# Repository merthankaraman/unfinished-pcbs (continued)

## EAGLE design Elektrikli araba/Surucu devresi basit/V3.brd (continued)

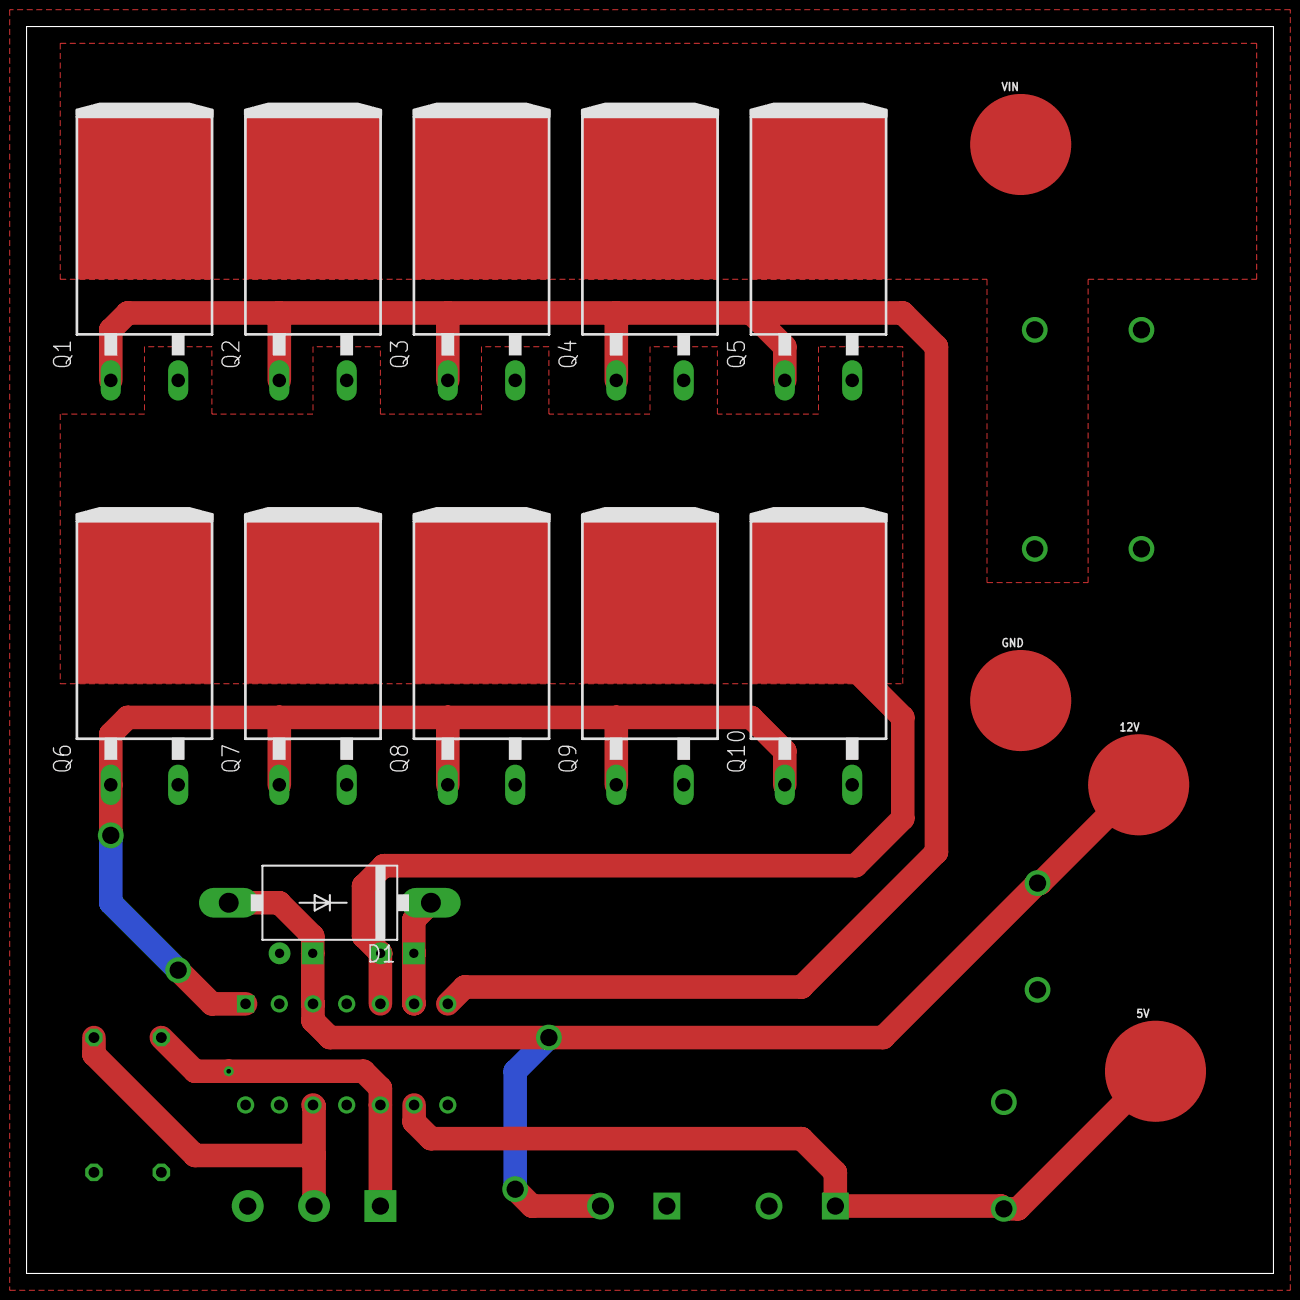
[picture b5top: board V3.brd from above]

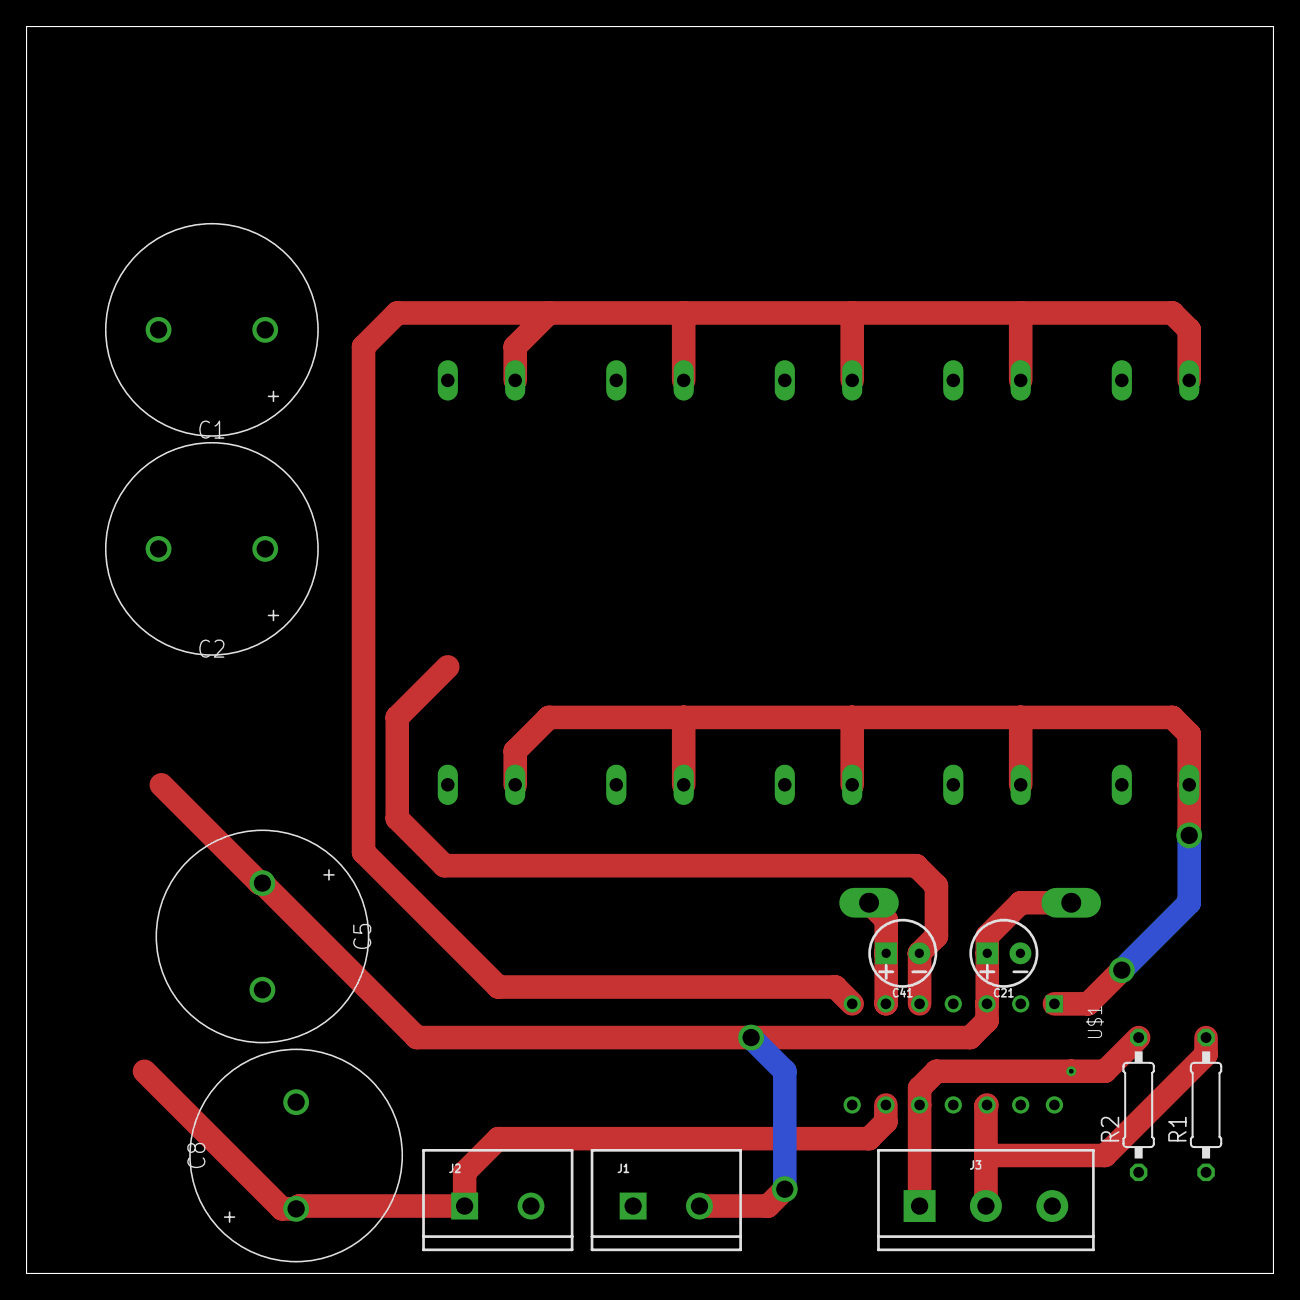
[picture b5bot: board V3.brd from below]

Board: 2 copper layers, 94.0 x 94.0 mm, 27 parts (12 on the bottom side), 10 nets.

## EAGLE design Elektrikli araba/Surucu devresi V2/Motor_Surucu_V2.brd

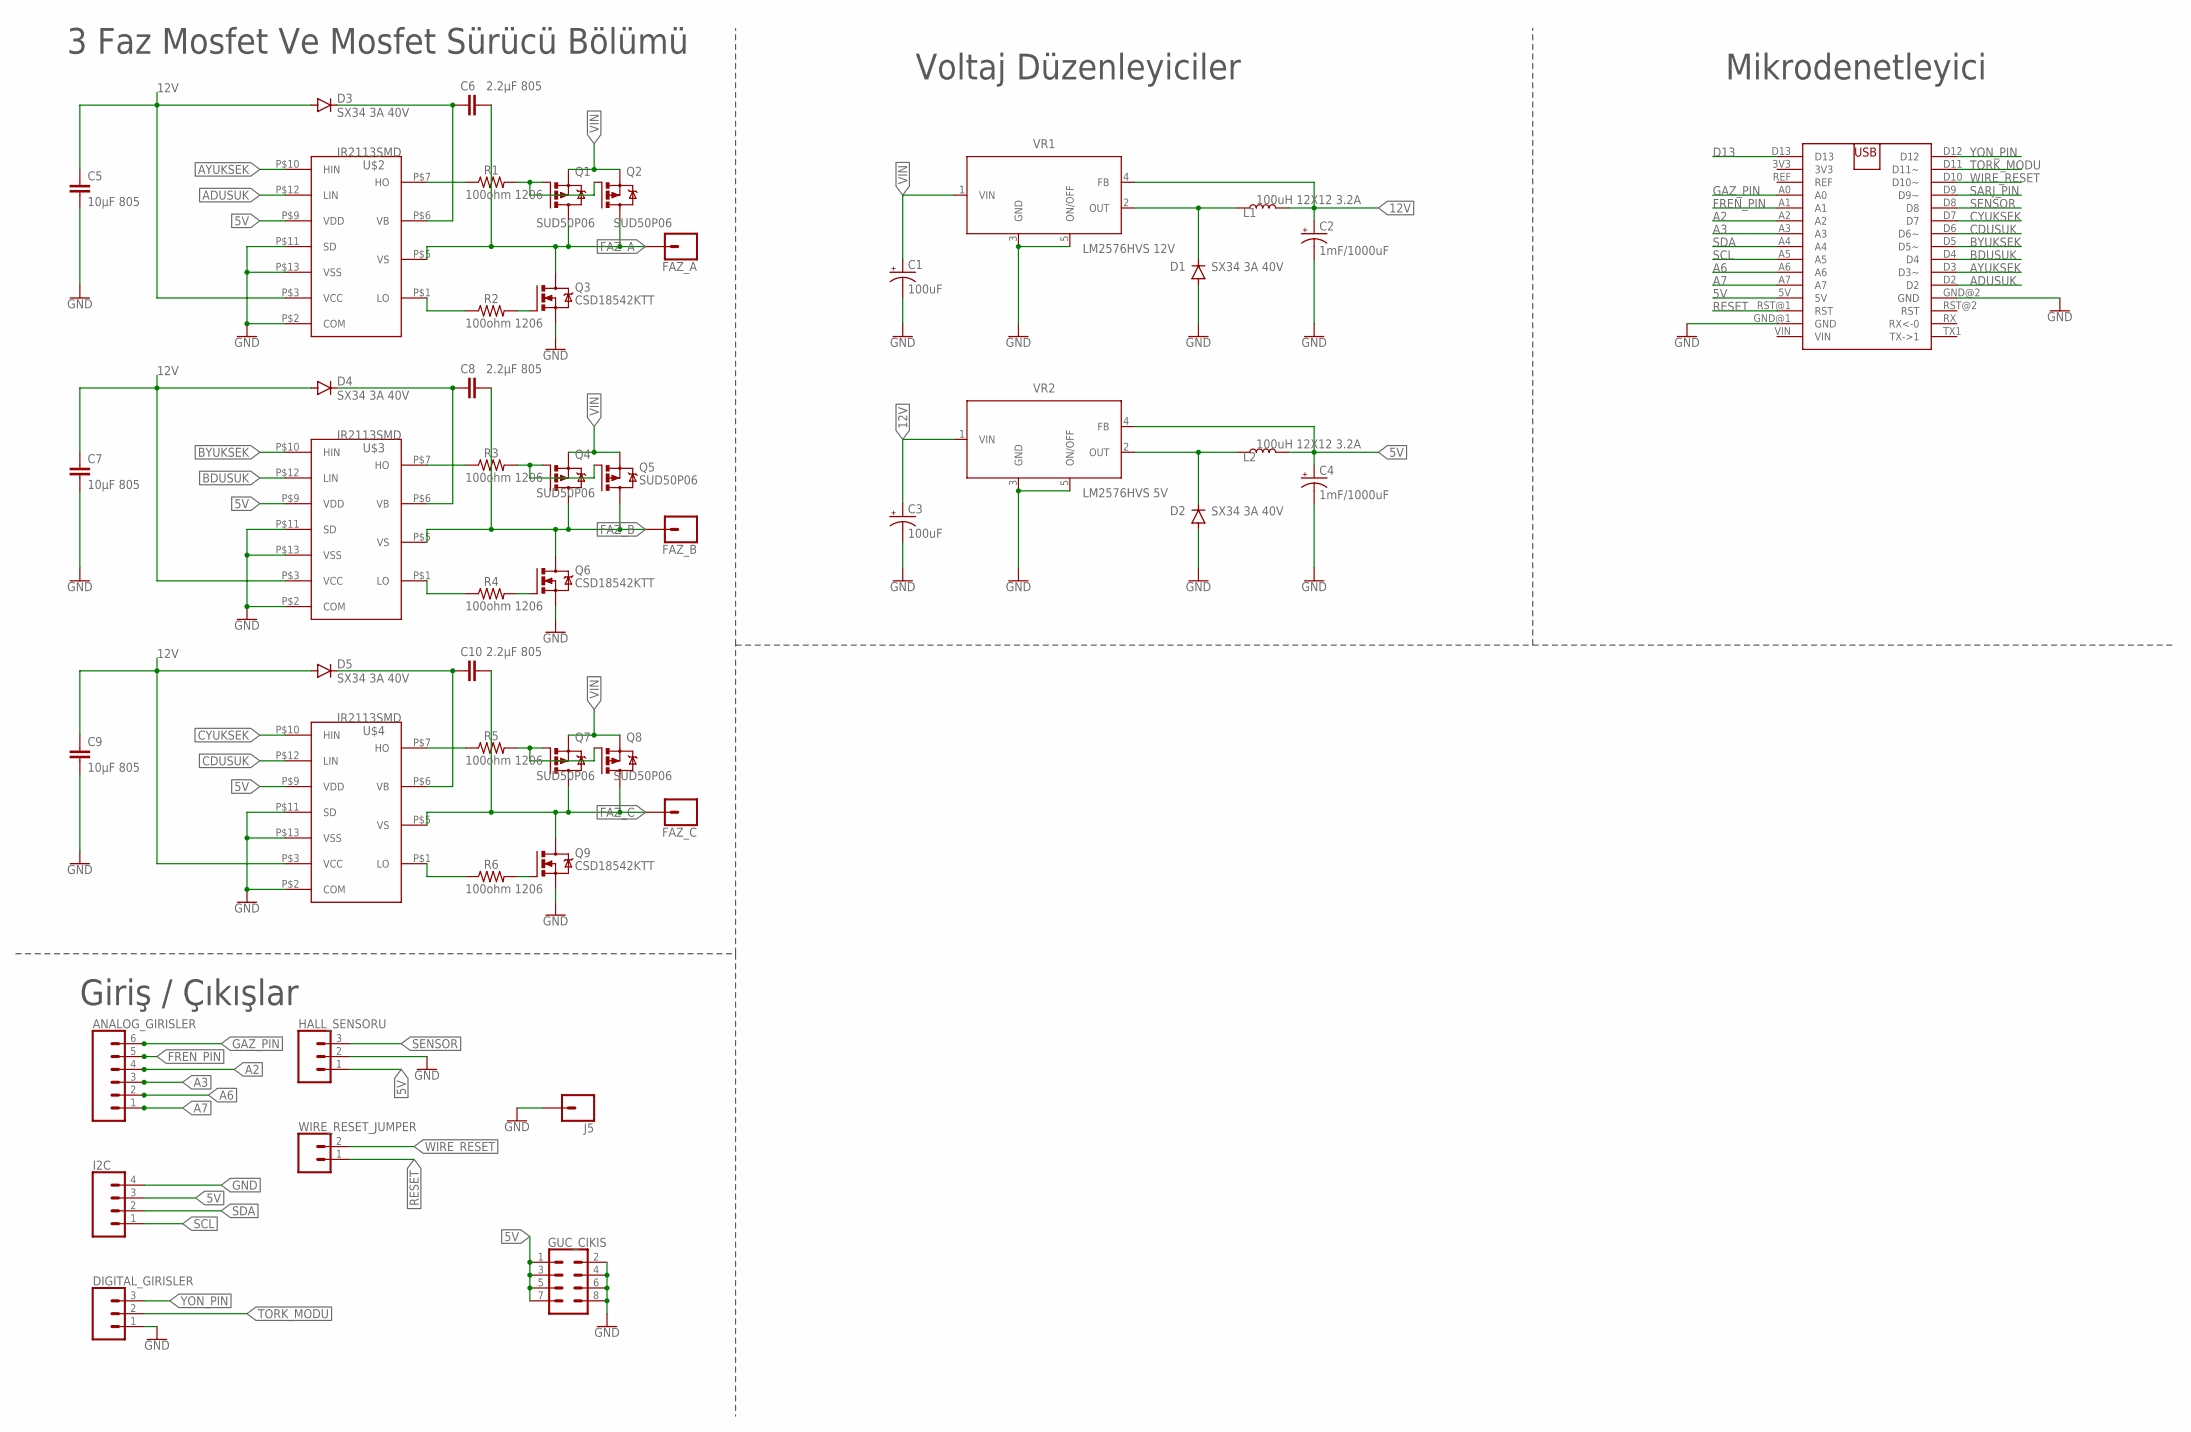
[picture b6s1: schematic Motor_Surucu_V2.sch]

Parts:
ANALOG_GIRISLER: CONN_06SILK_FEMALE_PTH; 1X06
C1, C3: 100uF; CPOL-RADIAL-2.5MM-6.5MM
C2, C4: 1mF/1000uF; PANASONIC_G
C5, C7, C9: 10µF 805; 0805
C6, C8, C10: 2.2µF 805; 0805
D1, D2, D3, D4, D5: SX34 3A 40V; DO214AC
DIGITAL_GIRISLER: CONN_03; 1X03
FAZ_A: CONN_01SNAP-MALE; SNAP-MALE
FAZ_B: CONN_01SNAP-MALE; SNAP-MALE
FAZ_C: CONN_01SNAP-MALE; SNAP-MALE
GUC_CIKIS: CONN_04X2; 2X4
HALL_SENSORU: CONN_03; 1X03
I2C: CONN_04; 1X04
J5: CONN_01SNAP-MALE; SNAP-MALE
L1, L2: 100uH 12X12 3.2A; INDUCTOR_SDR1307
Q1, Q2, Q4, Q5, Q7, Q8: SUD50P06; TO-252
Q3, Q6, Q9: CSD18542KTT; TO263-3
R1, R2, R3, R4, R5, R6: 100ohm 1206; 1206
U$1: ARDUINO_NANO
U$2, U$3, U$4: IR2113SMD; SOIC-14
VR1: LM2576HVS 12V; TO170P1435X465-6N
VR2: LM2576HVS 5V; TO170P1435X465-6N
WIRE_RESET_JUMPER: CONN_02; 1X02

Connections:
5V: C4.+, GUC_CIKIS.1, GUC_CIKIS.3, GUC_CIKIS.5, GUC_CIKIS.7, HALL_SENSORU.1, I2C.3, L2.P$2 (2), U$1.5V, U$2.P$9 (VDD), U$3.P$9 (VDD), U$4.P$9 (VDD), VR2.4 (FB)
12V: C2.+, C3.1 (+), C5.1, C7.1, C9.1, D3.A, D4.A, D5.A, L1.P$2 (2), U$2.P$3 (VCC), U$3.P$3 (VCC), U$4.P$3 (VCC), VR1.4 (FB), VR2.1 (VIN)
A2: ANALOG_GIRISLER.4, U$1.A2
A3: ANALOG_GIRISLER.3, U$1.A3
A6: ANALOG_GIRISLER.2, U$1.A6
A7: ANALOG_GIRISLER.1, U$1.A7
ADUSUK: U$1.D2, U$2.P$12 (LIN)
AYUKSEK: U$1.D3 (D3~), U$2.P$10 (HIN)
BDUSUK: U$1.D4, U$3.P$12 (LIN)
BYUKSEK: U$1.D5 (D5~), U$3.P$10 (HIN)
CDUSUK: U$1.D6 (D6~), U$4.P$12 (LIN)
CYUKSEK: U$1.D7, U$4.P$10 (HIN)
D13: U$1.D13
FAZ_A: C6.2, FAZ_A.2, Q1.TAB (D), Q2.TAB (D), Q3.TAB (D), U$2.P$5 (VS)
FAZ_B: C8.2, FAZ_B.2, Q4.TAB (D), Q5.TAB (D), Q6.TAB (D), U$3.P$5 (VS)
FAZ_C: C10.2, FAZ_C.2, Q7.TAB (D), Q8.TAB (D), Q9.TAB (D), U$4.P$5 (VS)
FREN_PIN: ANALOG_GIRISLER.5, U$1.A1
GAZ_PIN: ANALOG_GIRISLER.6, U$1.A0
GND: C1.2 (-), C2.-, C3.2 (-), C4.-, C5.2, C7.2, C9.2, D1.A, D2.A, DIGITAL_GIRISLER.1, GUC_CIKIS.2, GUC_CIKIS.4, GUC_CIKIS.6, GUC_CIKIS.8, HALL_SENSORU.2, I2C.4, J5.2, Q3.3 (S), Q6.3 (S), Q9.3 (S), U$1.GND@1 (GND), U$1.GND@2 (GND), U$2.P$2 (COM), U$2.P$11 (SD), U$2.P$13 (VSS), U$3.P$2 (COM), U$3.P$11 (SD), U$3.P$13 (VSS), U$4.P$2 (COM), U$4.P$11 (SD), U$4.P$13 (VSS), VR1.3 (GND), VR1.5 (ON/OFF), VR2.3 (GND), VR2.5 (ON/OFF)
unnamed: D2.C, L2.P$1 (1), VR2.2 (OUT)
unnamed: C6.1, D3.C, U$2.P$6 (VB)
unnamed: Q1.1 (G), Q2.1 (G), R1.2
unnamed: R1.1, U$2.P$7 (HO)
unnamed: Q3.1 (G), R2.2
unnamed: R2.1, U$2.P$1 (LO)
unnamed: C8.1, D4.C, U$3.P$6 (VB)
unnamed: Q4.1 (G), Q5.1 (G), R3.2
unnamed: R3.1, U$3.P$7 (HO)
unnamed: Q6.1 (G), R4.2
unnamed: R4.1, U$3.P$1 (LO)
unnamed: C10.1, D5.C, U$4.P$6 (VB)
unnamed: Q7.1 (G), Q8.1 (G), R5.2
unnamed: R5.1, U$4.P$7 (HO)
unnamed: Q9.1 (G), R6.2
unnamed: R6.1, U$4.P$1 (LO)
unnamed: D1.C, L1.P$1 (1), VR1.2 (OUT)
RESET: U$1.RST@1 (RST), WIRE_RESET_JUMPER.1
SARJ_PIN: U$1.D9 (D9~)
SCL: I2C.1, U$1.A5
SDA: I2C.2, U$1.A4
SENSOR: HALL_SENSORU.3, U$1.D8
TORK_MODU: DIGITAL_GIRISLER.2, U$1.D11 (D11~)
VIN: C1.1 (+), Q1.3 (S), Q2.3 (S), Q4.3 (S), Q5.3 (S), Q7.3 (S), Q8.3 (S), VR1.1 (VIN)
WIRE_RESET: U$1.D10 (D10~), WIRE_RESET_JUMPER.2
YON_PIN: DIGITAL_GIRISLER.3, U$1.D12

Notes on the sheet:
3 Faz Mosfet Ve Mosfet Sürücü Bölümü
Voltaj Düzenleyiciler
Mikrodenetleyici
Giriş / Çıkışlar

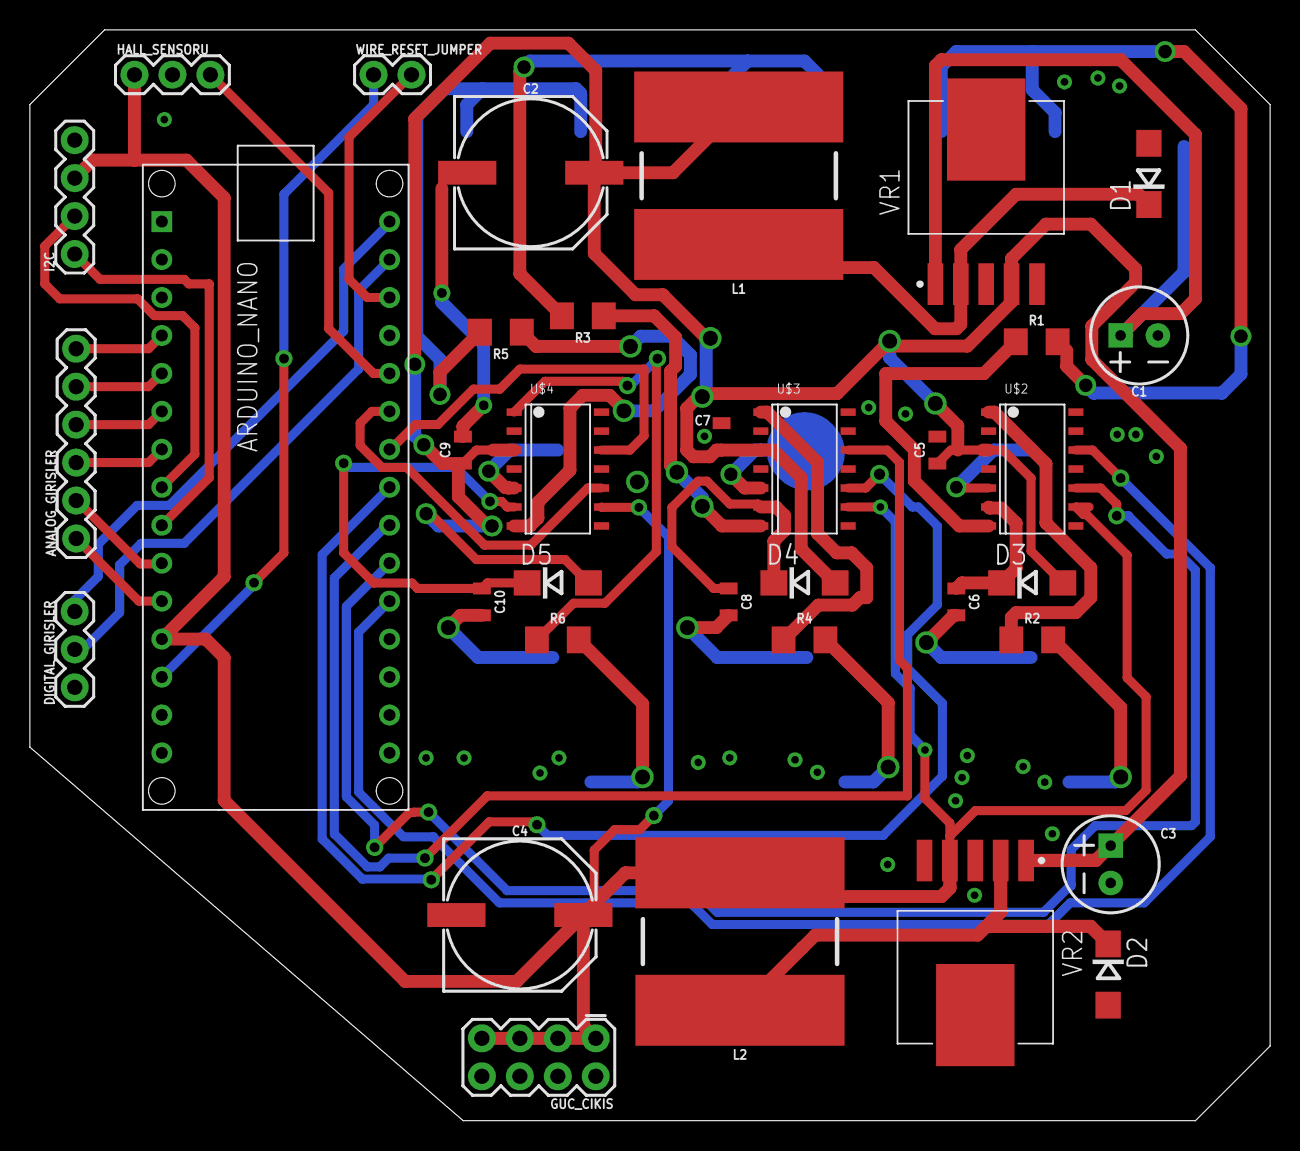
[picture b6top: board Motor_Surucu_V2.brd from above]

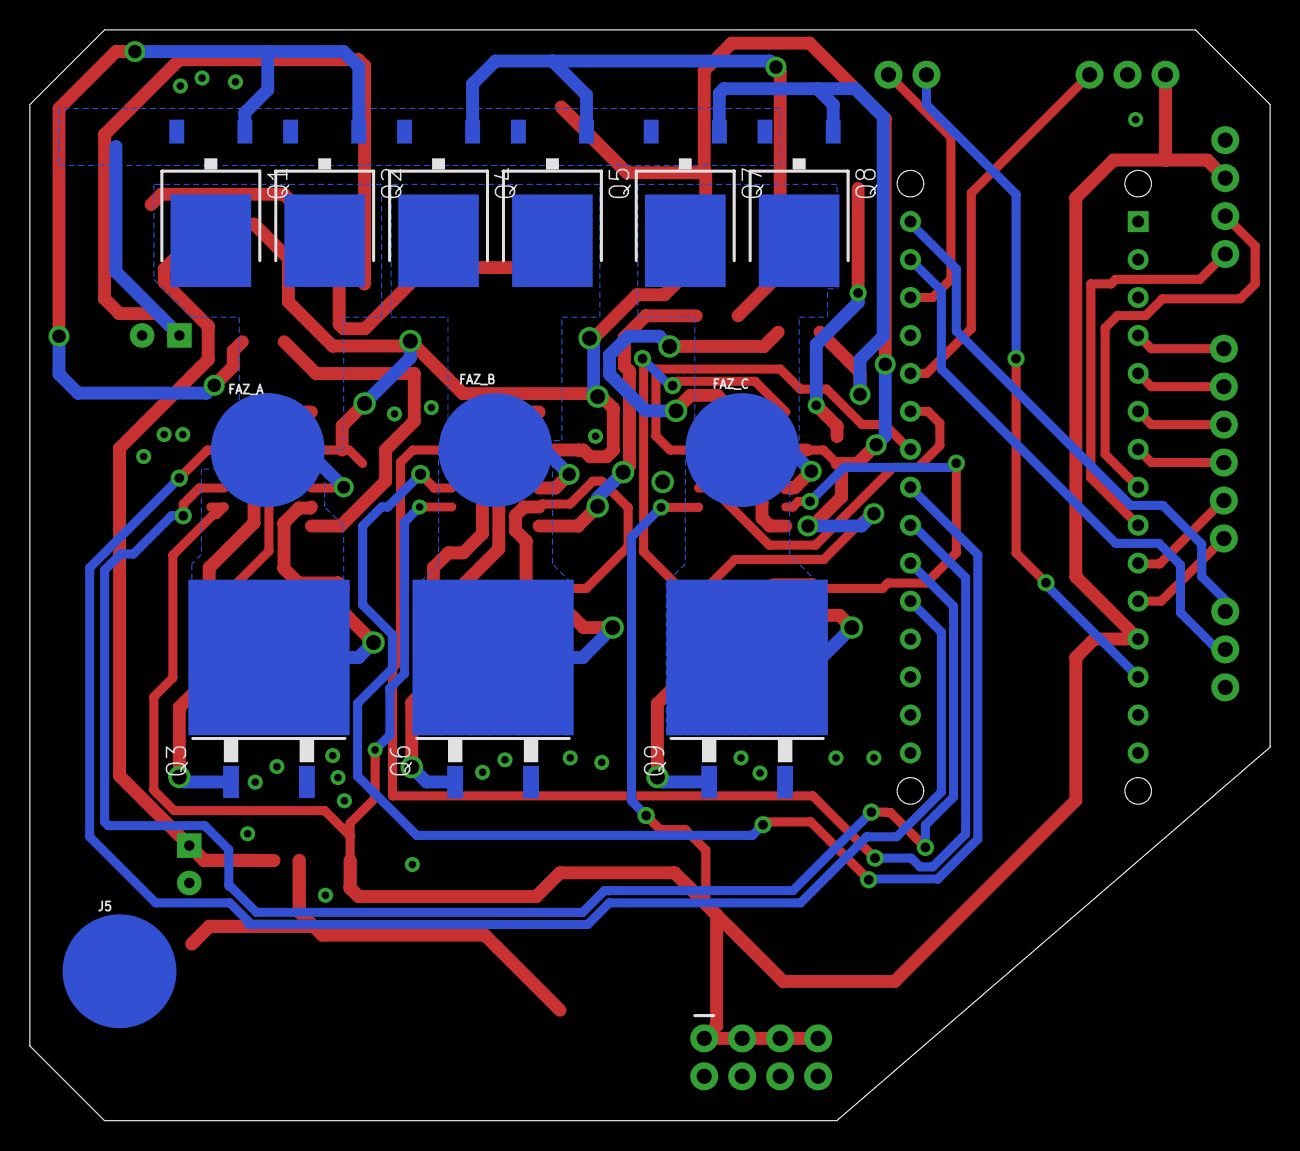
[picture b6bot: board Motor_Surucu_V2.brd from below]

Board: 2 copper layers, 83.0 x 73.0 mm, 48 parts (13 on the bottom side), 43 nets.

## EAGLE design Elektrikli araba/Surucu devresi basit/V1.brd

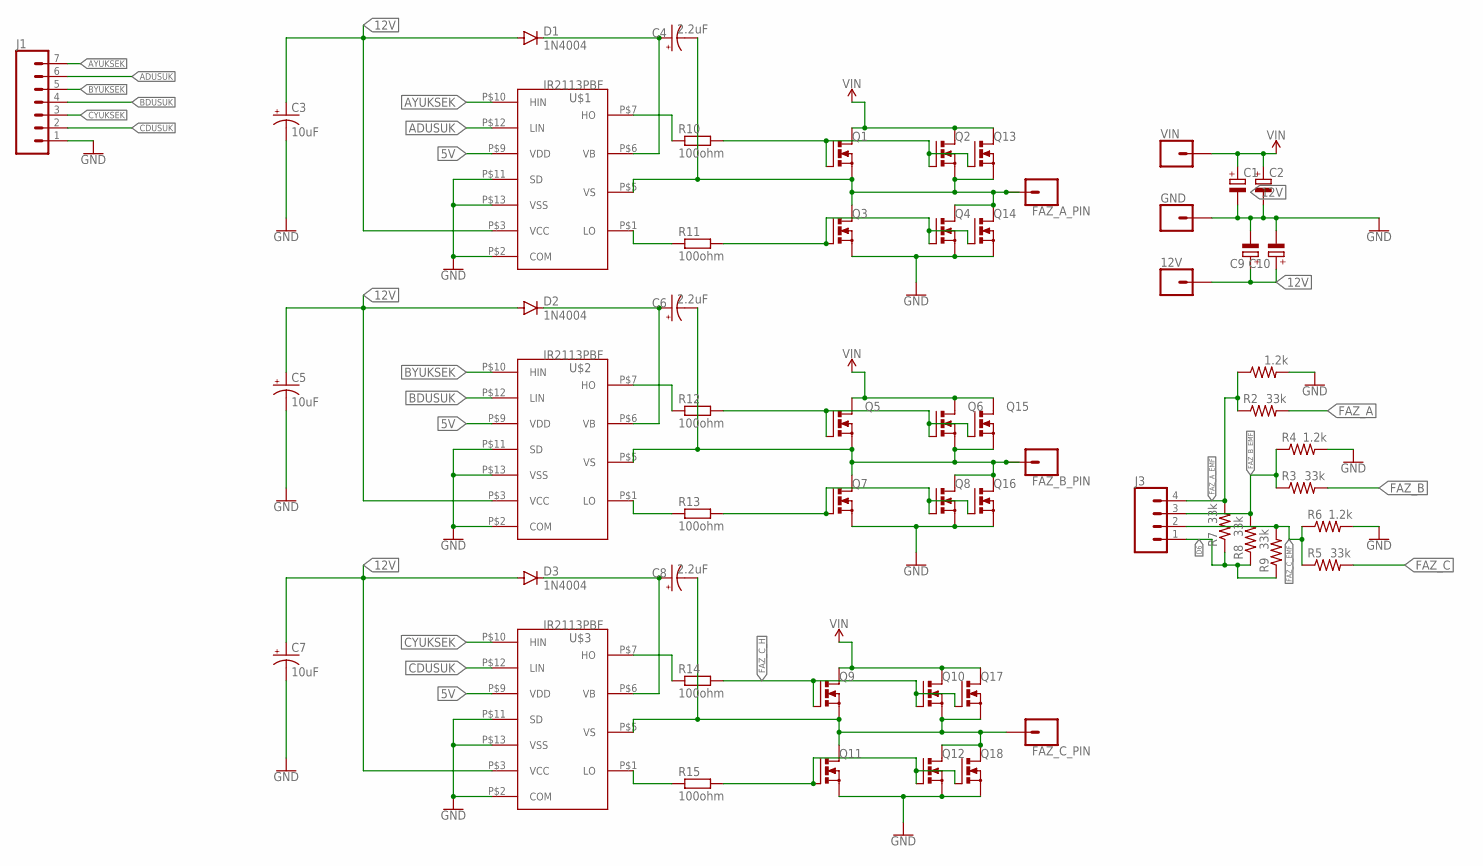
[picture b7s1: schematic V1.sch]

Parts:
12V: CONN_01SNAP-MALE; SNAP-MALE
C1, C2, C9, C10: C-POL_RADIAL-25MM-DIA; CAPPRD550W110D1250H2500B
C3, C5, C7: 10uF; CPOL-RADIAL-2.5MM-5MM
C4, C6, C8: 2.2uF; CPOL-RADIAL-2.5MM-5MM
D1, D2, D3: 1N4004; DO41-10
FAZ_A_PIN: CONN_01SNAP-MALE; SNAP-MALE
FAZ_B_PIN: CONN_01SNAP-MALE; SNAP-MALE
FAZ_C_PIN: CONN_01SNAP-MALE; SNAP-MALE
GND: CONN_01SNAP-MALE; SNAP-MALE
J1: CONN_07; 1X07
J3: CONN_04; 1X04
Q1, Q2, Q3, Q4, Q5, Q6, Q7, Q8, Q9, Q10, Q11, Q12, Q13, Q14, Q15, Q16, Q17, Q18: PMOSFET_NTO220BV; TO220BV
R1, R4, R6: 1.2k; AXIAL-0.3
R2, R3, R5, R7, R8, R9: 33k; AXIAL-0.3
R10, R11, R12, R13, R14, R15: 100ohm; 0207/10
U$1, U$2, U$3: IR2113PBF; PDIP-14
VIN: CONN_01SNAP-MALE; SNAP-MALE

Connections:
5V: U$1.P$9 (VDD), U$2.P$9 (VDD), U$3.P$9 (VDD)
12V: 12V.2, C3.1 (+), C5.1 (+), C7.1 (+), C9.1 (+), C10.1 (+), D1.A, D2.A, D3.A, U$1.P$3 (VCC), U$2.P$3 (VCC), U$3.P$3 (VCC)
ADUSUK: J1.6, U$1.P$12 (LIN)
AYUKSEK: J1.7, U$1.P$10 (HIN)
BDUSUK: J1.4, U$2.P$12 (LIN)
BYUKSEK: J1.5, U$2.P$10 (HIN)
CDUSUK: J1.2, U$3.P$12 (LIN)
CYUKSEK: J1.3, U$3.P$10 (HIN)
D6: J3.1, R7.P$1 (1), R8.P$1 (1), R9.P$1 (1)
FAZ_A: C4.2 (-), FAZ_A_PIN.2, Q1.S, Q2.S, Q3.D, Q4.D, Q13.S, Q14.D, R2.P$2 (2), U$1.P$5 (VS)
FAZ_A_EMF: J3.4, R1.P$1 (1), R2.P$1 (1), R7.P$2 (2)
FAZ_A_H: Q1.G, Q2.G, Q13.G, R10.2
FAZ_A_L: Q3.G, Q4.G, Q14.G, R11.2
FAZ_B: C6.2 (-), FAZ_B_PIN.2, Q5.S, Q6.S, Q7.D, Q8.D, Q15.S, Q16.D, R3.P$2 (2), U$2.P$5 (VS)
FAZ_B_EMF: J3.3, R3.P$1 (1), R4.P$1 (1), R8.P$2 (2)
FAZ_B_H: Q5.G, Q6.G, Q15.G, R12.2
FAZ_B_L: Q7.G, Q8.G, Q16.G, R13.2
FAZ_C: C8.2 (-), FAZ_C_PIN.2, Q9.S, Q10.S, Q11.D, Q12.D, Q17.S, Q18.D, R5.P$2 (2), U$3.P$5 (VS)
FAZ_C_EMF: J3.2, R5.P$1 (1), R6.P$1 (1), R9.P$2 (2)
FAZ_C_H: Q9.G, Q10.G, Q17.G, R14.2
FAZ_C_L: Q11.G, Q12.G, Q18.G, R15.2
GND: C1.2 (-), C2.2 (-), C3.2 (-), C5.2 (-), C7.2 (-), C9.2 (-), C10.2 (-), GND.2, J1.1, Q3.S, Q4.S, Q7.S, Q8.S, Q11.S, Q12.S, Q14.S, Q16.S, Q18.S, R1.P$2 (2), R4.P$2 (2), R6.P$2 (2), U$1.P$2 (COM), U$1.P$11 (SD), U$1.P$13 (VSS), U$2.P$2 (COM), U$2.P$11 (SD), U$2.P$13 (VSS), U$3.P$2 (COM), U$3.P$11 (SD), U$3.P$13 (VSS)
unnamed: C6.1 (+), D2.C, U$2.P$6 (VB)
unnamed: R13.1, U$2.P$1 (LO)
unnamed: R12.1, U$2.P$7 (HO)
unnamed: C4.1 (+), D1.C, U$1.P$6 (VB)
unnamed: C8.1 (+), D3.C, U$3.P$6 (VB)
unnamed: R10.1, U$1.P$7 (HO)
unnamed: R15.1, U$3.P$1 (LO)
unnamed: R11.1, U$1.P$1 (LO)
unnamed: R14.1, U$3.P$7 (HO)
VIN: C1.1 (+), C2.1 (+), Q1.D, Q2.D, Q5.D, Q6.D, Q9.D, Q10.D, Q13.D, Q15.D, Q17.D, VIN.2

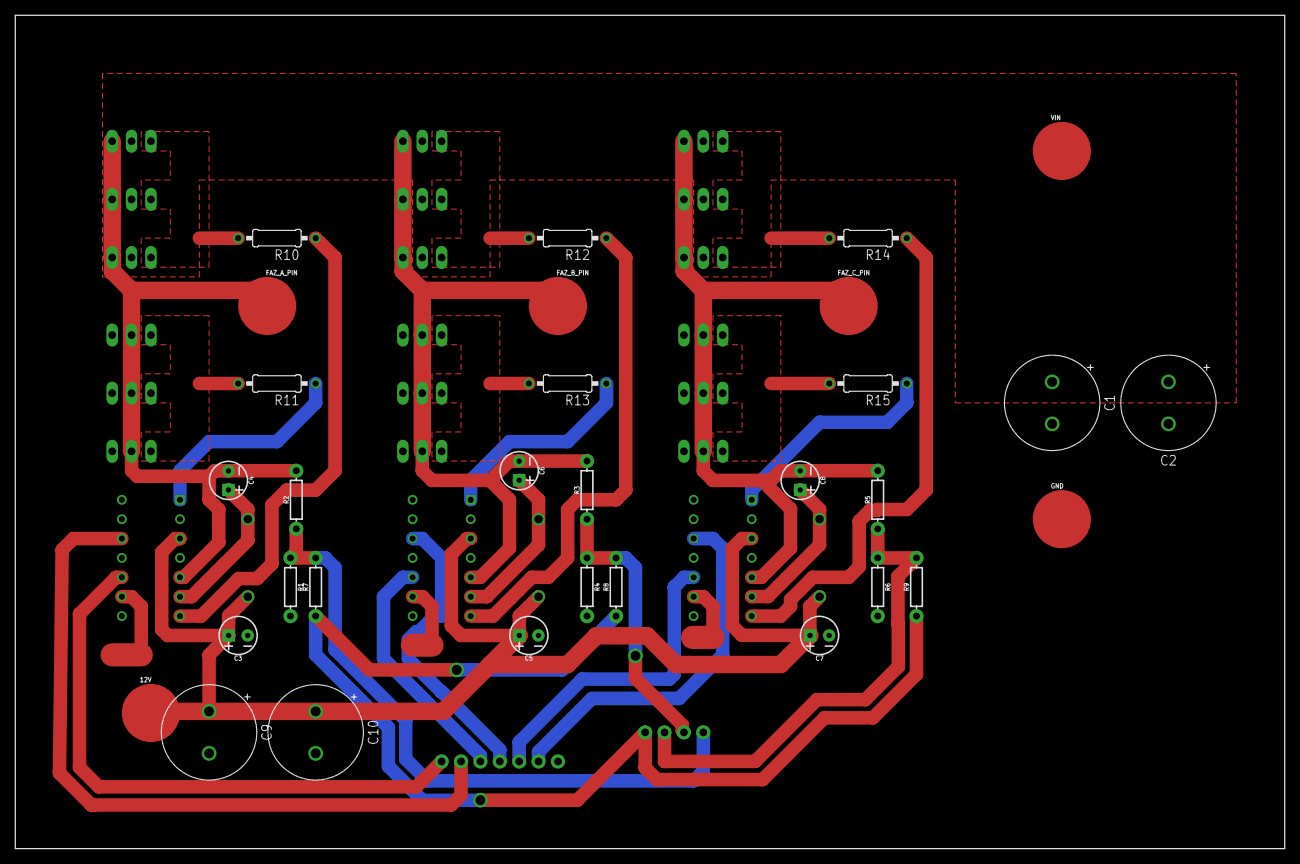
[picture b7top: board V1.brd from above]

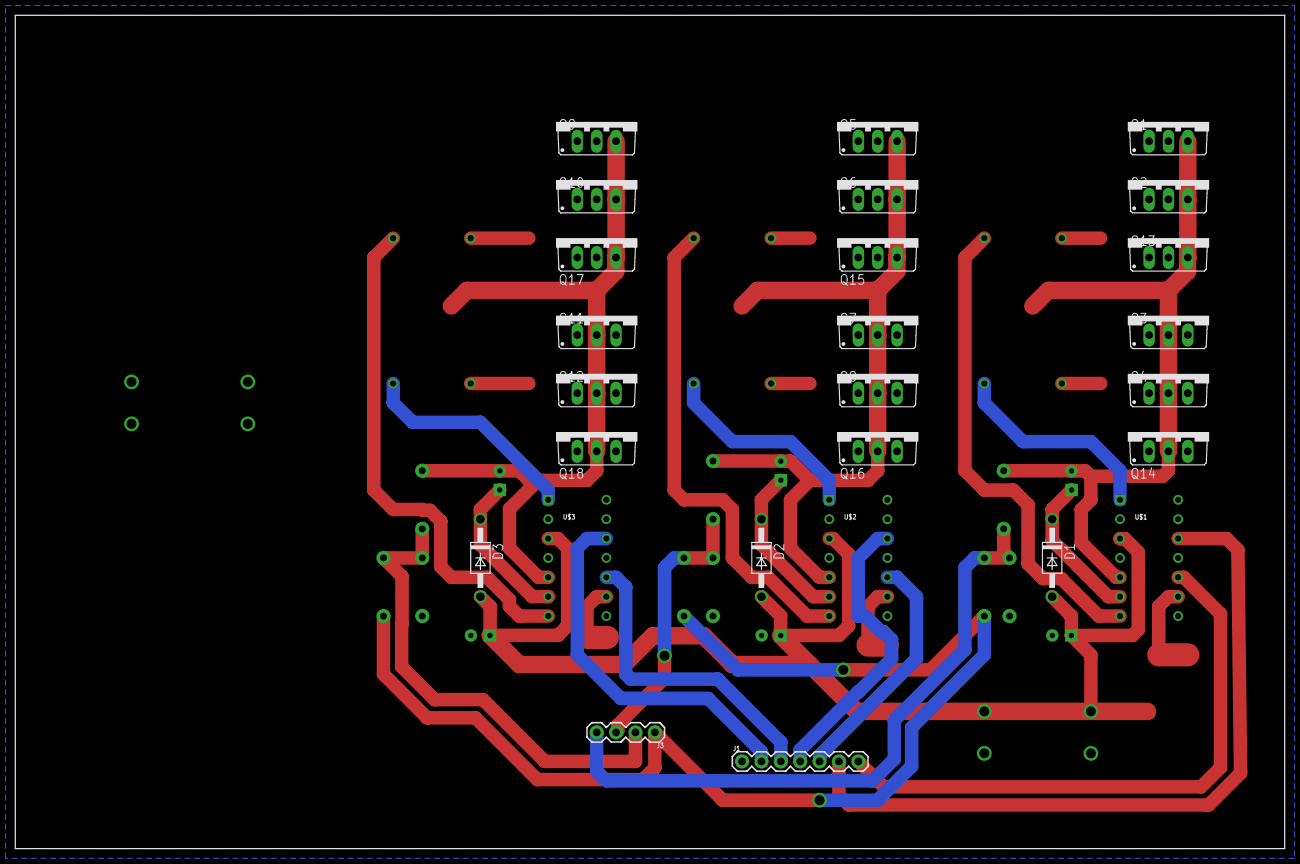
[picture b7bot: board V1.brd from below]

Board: 2 copper layers, 166.4 x 109.2 mm, 57 parts (26 on the bottom side), 32 nets.

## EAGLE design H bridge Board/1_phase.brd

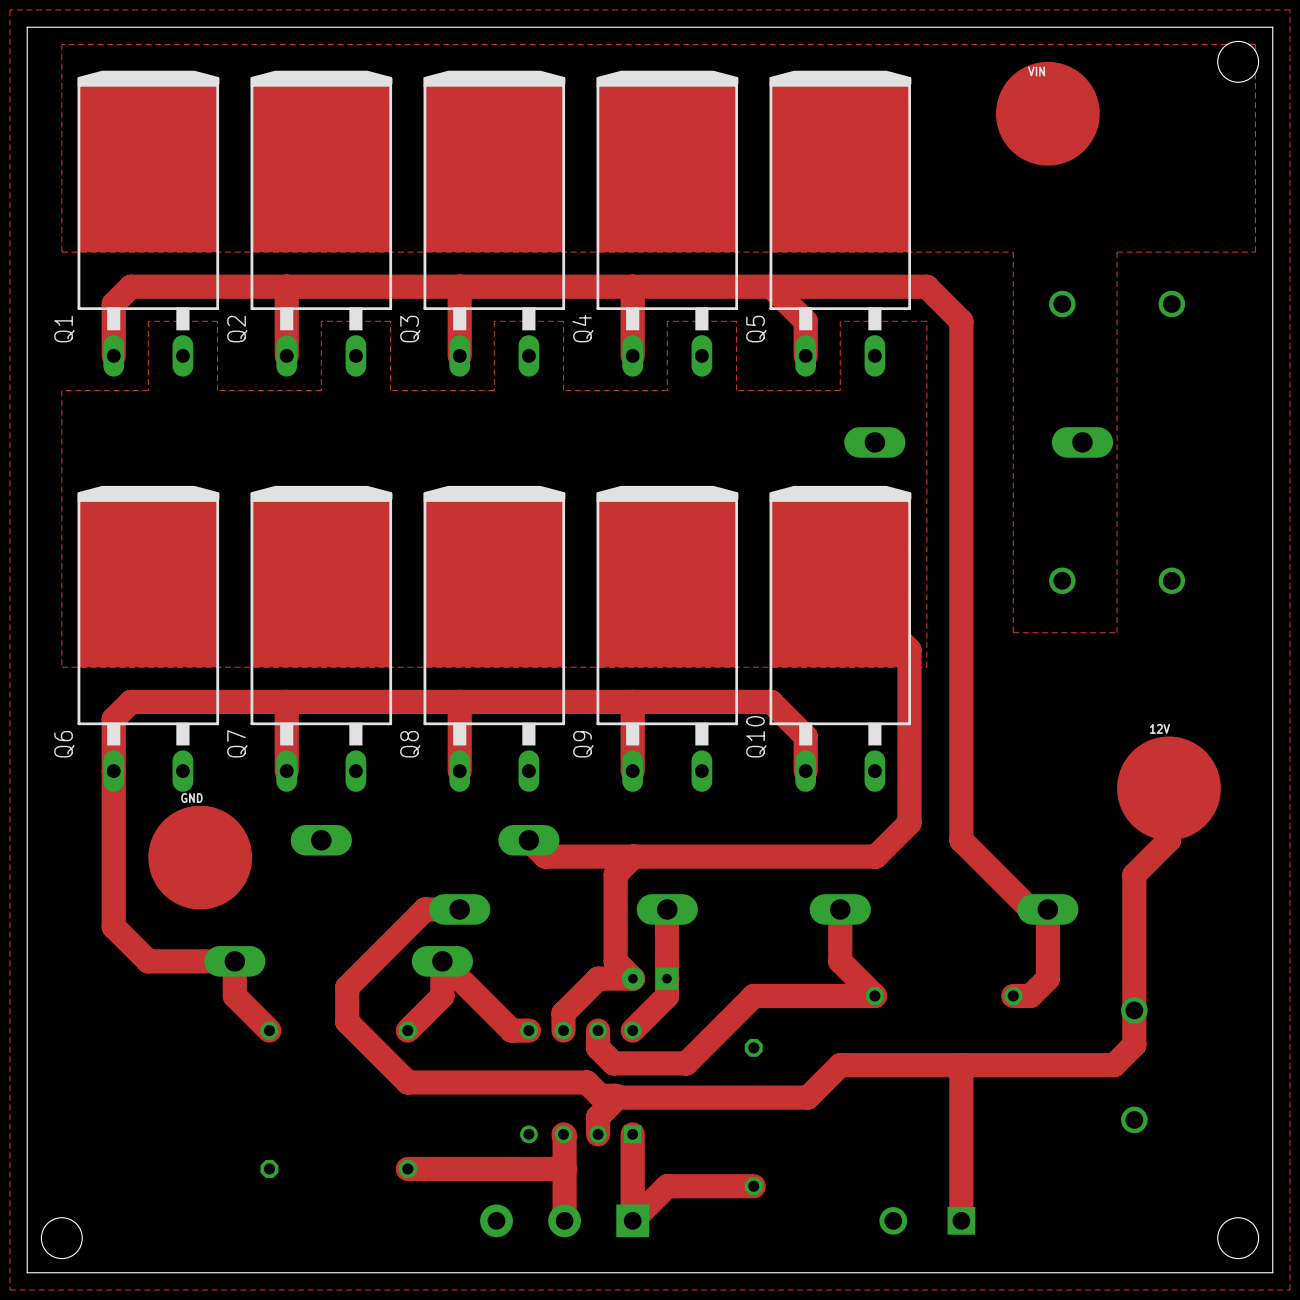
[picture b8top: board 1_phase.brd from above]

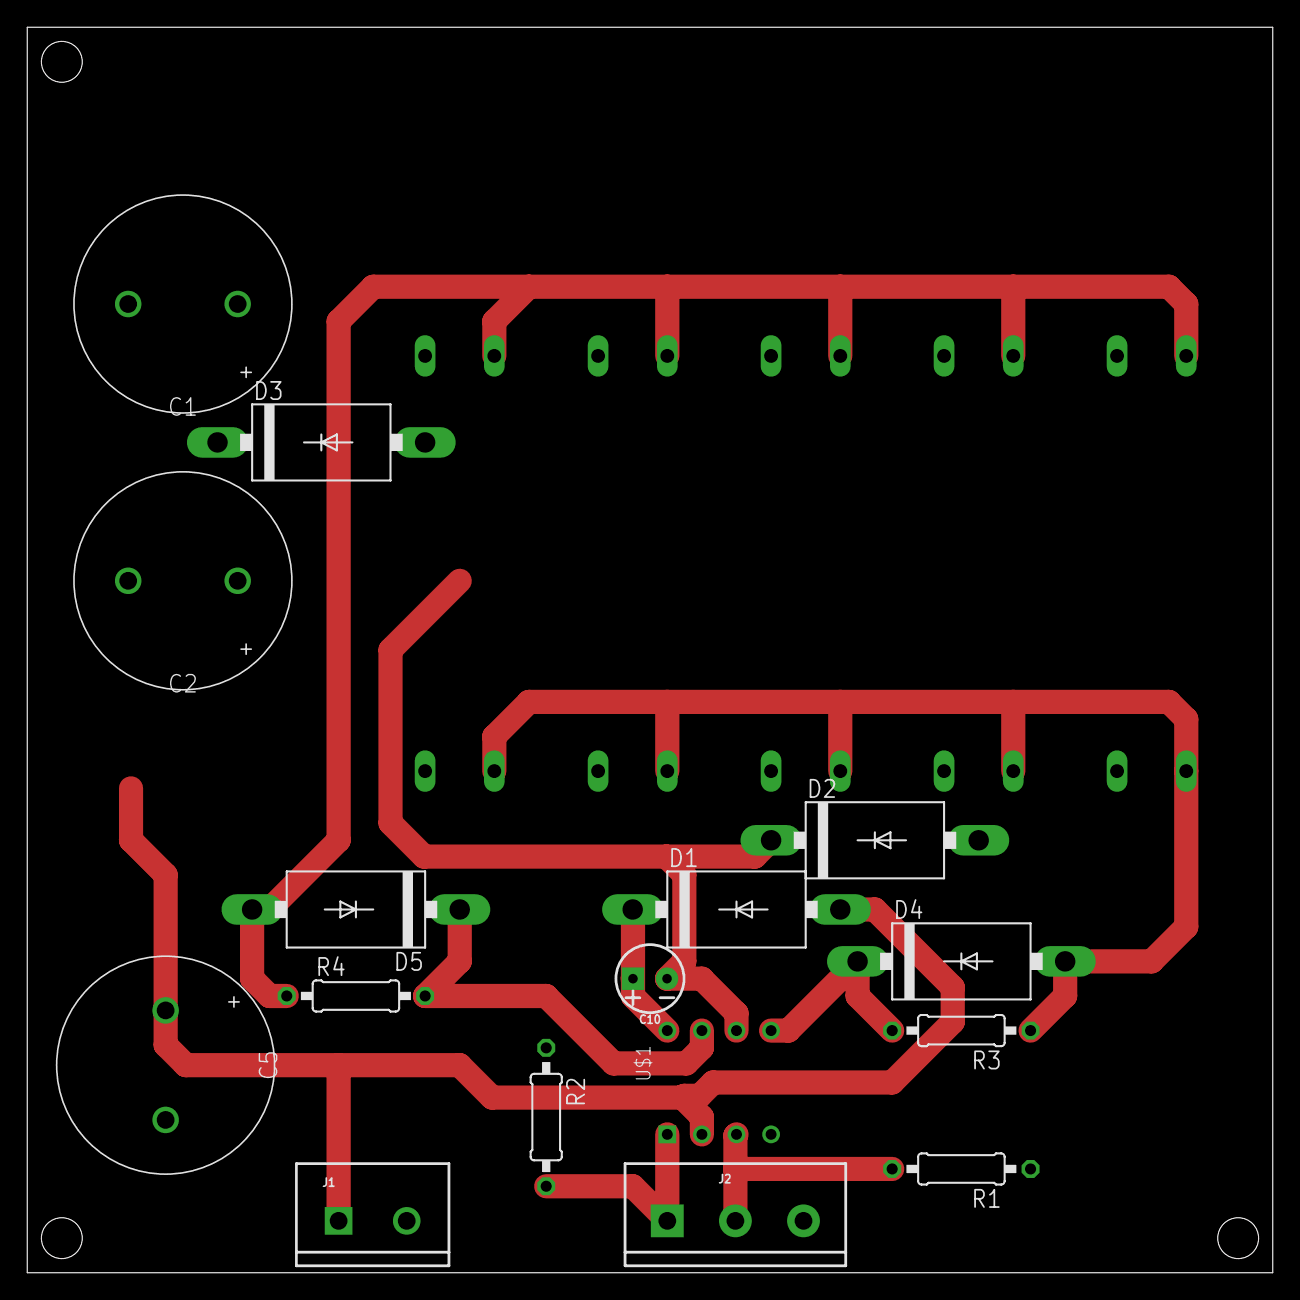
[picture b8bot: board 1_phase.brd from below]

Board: 2 copper layers, 91.4 x 91.4 mm, 29 parts (16 on the bottom side), 11 nets.

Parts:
12V: SNAP-MALE
C1, C2, C5: 16MM-DIA-CAPASITOR
C10: 2.2uF; CPOL-RADIAL-2.5MM-5MM
D1, D2, D3, D4, D5: 1N5400; DO201-15
GND: SNAP-MALE
J1: SCREWTERMINAL-5MM-2
J2: SCREWTERMINAL-5MM-3
Q1, Q2, Q3, Q4, Q5, Q6, Q7, Q8, Q9, Q10: IRF640N; TO-220-PAD
R1, R2: 10k; 0207/10
R3, R4: 27; 0207/10
U$1: IR2104PBF; DIP-8
VIN: SNAP-MALE

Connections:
12V: 12V.2, C5.+, D1.A, J1.1, U$1.2
FAZ: C10.2, D2.C, D3.A, Q1.3, Q2.3, Q3.3, Q4.3, Q5.3, Q6.TAB, Q7.TAB, Q8.TAB, Q9.TAB, Q10.TAB, U$1.6
FAZ_A_L: D4.A, Q6.1, Q7.1, Q8.1, Q9.1, Q10.1, R3.1
FAZ_IN: J2.1, R2.2, U$1.1
FAZ_ON: J2.2, R1.2, U$1.3
GND: C1.-, C2.-, C5.-, D2.A, GND.2, J1.2, J2.3, Q6.3, Q7.3, Q8.3, Q9.3, Q10.3, R1.1, R2.1, U$1.4
unnamed: D5.A, Q1.1, Q2.1, Q3.1, Q4.1, Q5.1, R4.1
unnamed: C10.1, D1.C, U$1.8
unnamed: D4.C, R3.2, U$1.5
unnamed: D5.C, R4.2, U$1.7
VIN: C1.+, C2.+, D3.C, Q1.TAB, Q2.TAB, Q3.TAB, Q4.TAB, Q5.TAB, VIN.2

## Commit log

2023-01-29 BMS klasörü eklendi
2023-01-29 Elektrikli araba hakkındaki çalışmalar yüklendi
    Elektrikli araba hakkındaki çalışmalarının ilk yarısı yüklendi
2023-01-29 Elektrikli araba hakkındaki çalışmalar yüklendi
    Elektrikli araba hakkındaki çalışmaların son kısmı yüklendi
2023-01-29 gitignore eklendi
2023-01-29 Kalan klasörler eklendi
